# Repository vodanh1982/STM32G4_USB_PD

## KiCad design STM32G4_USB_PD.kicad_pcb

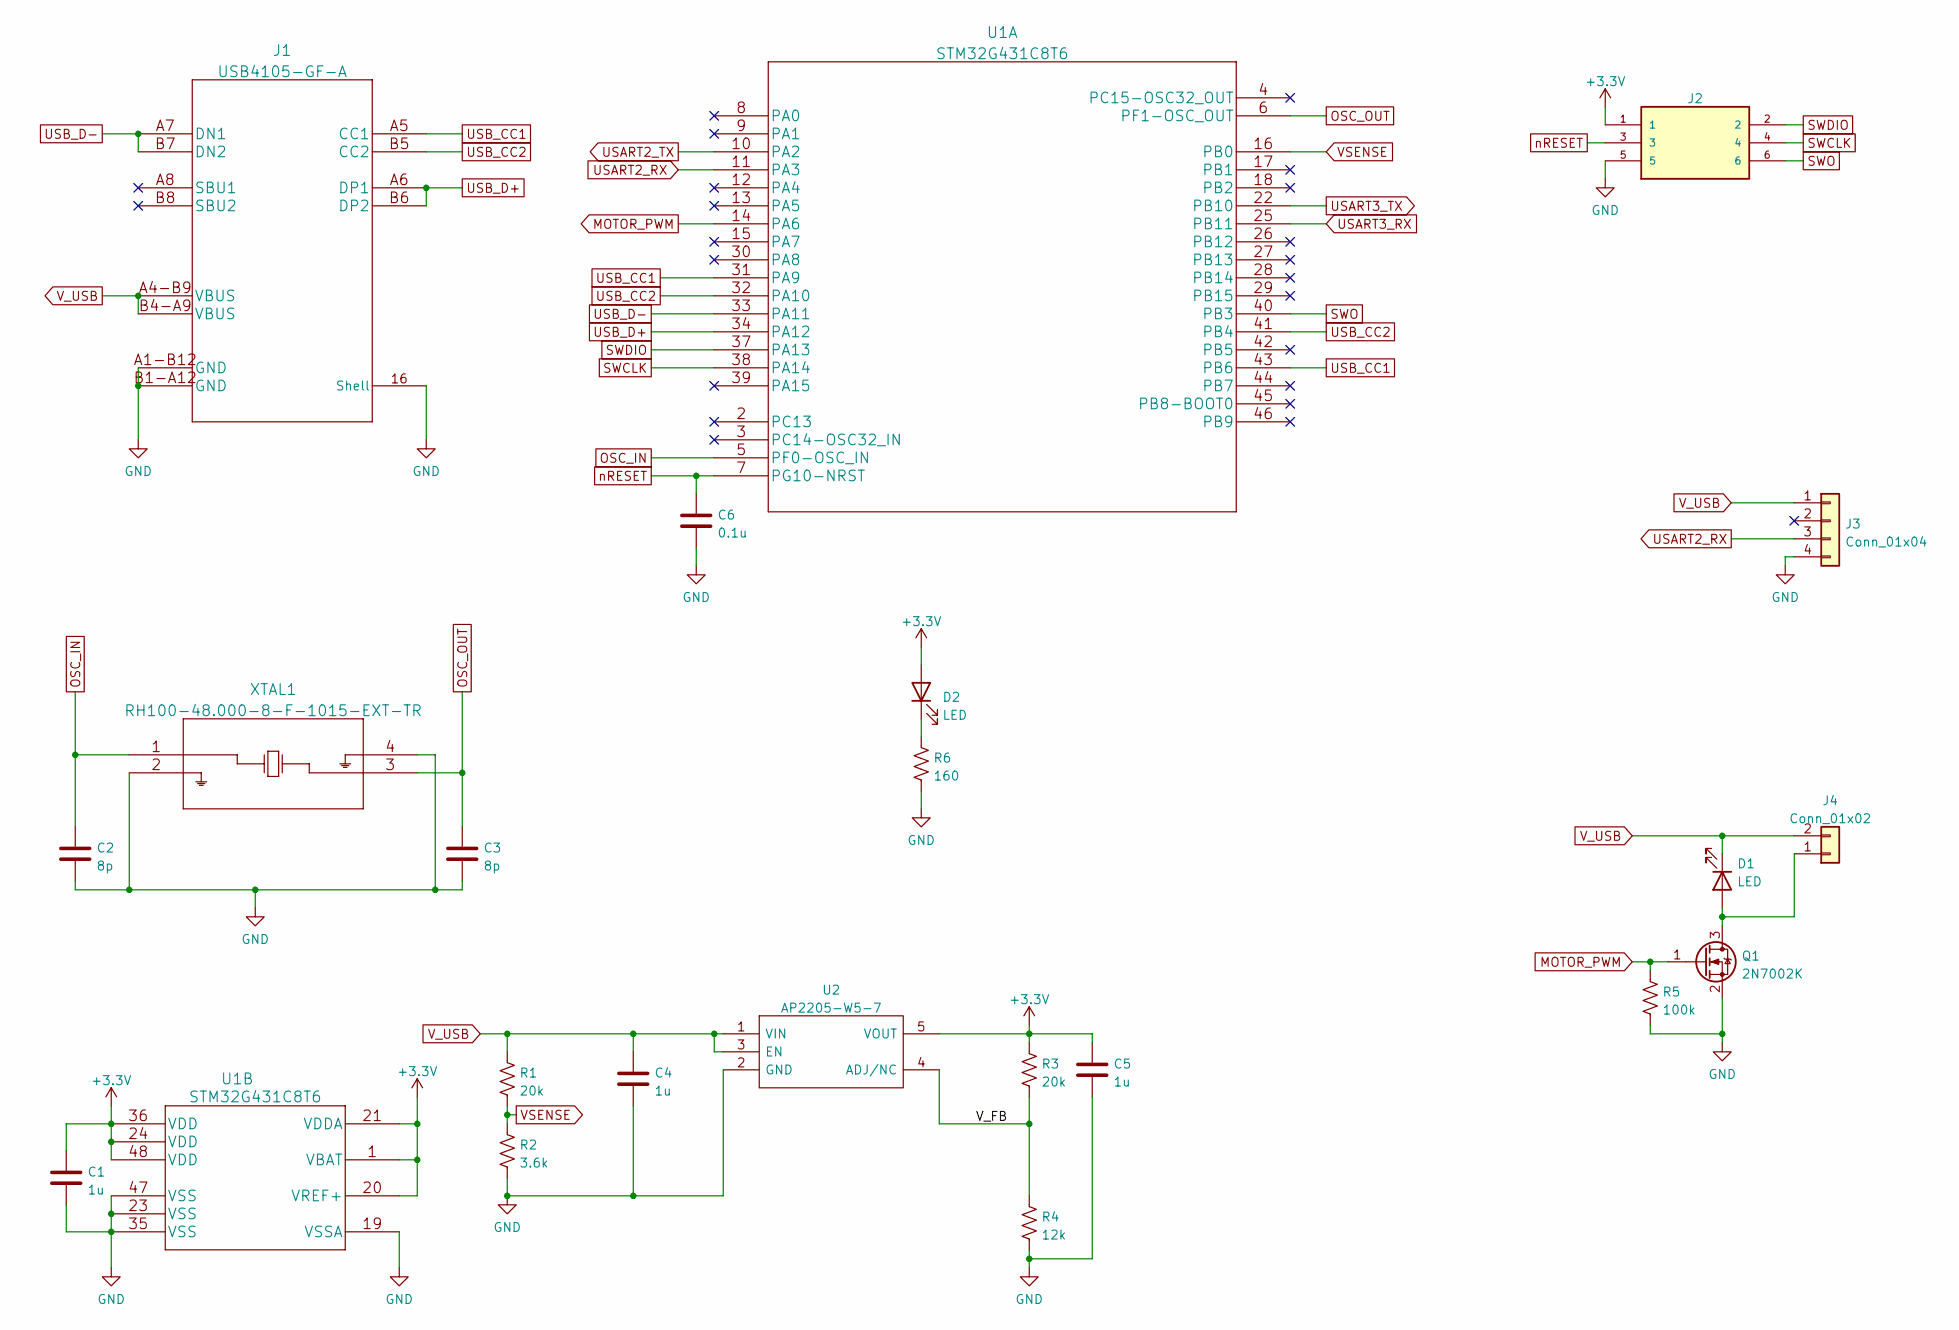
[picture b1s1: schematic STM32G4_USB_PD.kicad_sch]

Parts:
C1, C4, C5: 1u; C_0603_1608Metric_Pad1.08x0.95mm_HandSolder
C2, C3: 8p; C_0201_0603Metric_Pad0.64x0.40mm_HandSolder
C6: 0.1u; C_0201_0603Metric_Pad0.64x0.40mm_HandSolder
D1, D2: LED; LED_0603_1608Metric_Pad1.05x0.95mm_HandSolder
J1: USB4105-GF-A
J2: 8.06.16_J-LINK_6-PIN_NEEDLE_ADAPTER; J-LINK_6-PIN_NEEDLE_ADAPTER; PARTREV A
J3: Conn_01x04; JST_PH_2mm_4
J4: Conn_01x02; JST_PH_2mm_2
Q1: 2N7002K; SOT-23
R1, R3: 20k; R_0603_1608Metric_Pad0.98x0.95mm_HandSolder
R2: 3.6k; R_0603_1608Metric_Pad0.98x0.95mm_HandSolder
R4: 12k; R_0603_1608Metric_Pad0.98x0.95mm_HandSolder
R5: 100k; R_0603_1608Metric_Pad0.98x0.95mm_HandSolder
R6: 160; R_0603_1608Metric_Pad0.98x0.95mm_HandSolder
U1: STM32G431C8T6
U2: AP2205-W5-7; SOT95P282X145-5N; Manufacturer_Part_Number AP2205-W5-7; Mouser Part Number 621-AP2205-W5-7
XTAL1: RH100-48.000-8-F-1015-EXT-TR

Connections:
+3.3V: C1.1, C5.1, D2.2 (A), J2.1, R3.1, U1.1 (VBAT), U1.20 (VREF+), U1.21 (VDDA), U1.24 (VDD), U1.36 (VDD), U1.48 (VDD), U2.5 (VOUT)
/V_FB: R3.2, R4.1, U2.4 (ADJ/NC)
MOTOR_PWM: Q1.1 (G), R5.1, U1.14 (PA6)
unnamed: D1.2 (A), J4.1, Q1.3 (D)
unnamed: D2.1 (K), R6.1
OSC_IN: C2.1, U1.5 (PF0-OSC_IN), XTAL1.1
OSC_OUT: C3.1, U1.6 (PF1-OSC_OUT), XTAL1.3
SWCLK: J2.4, U1.38 (PA14)
SWDIO: J2.2, U1.37 (PA13)
SWO: J2.6, U1.40 (PB3)
USART2_RX: J3.3, U1.11 (PA3)
USART2_TX: U1.10 (PA2)
USART3_RX: U1.25 (PB11)
USART3_TX: U1.22 (PB10)
USB_CC1: J1.A5 (CC1), U1.31 (PA9), U1.43 (PB6)
USB_CC2: J1.B5 (CC2), U1.32 (PA10), U1.41 (PB4)
USB_D+: J1.A6 (DP1), J1.B6 (DP2), U1.34 (PA12)
USB_D-: J1.A7 (DN1), J1.B7 (DN2), U1.33 (PA11)
VSENSE: R1.2, R2.1, U1.16 (PB0)
V_USB: C4.1, D1.1 (K), J1.A4-B9 (VBUS), J1.B4-A9 (VBUS), J3.1, J4.2, R1.1, U2.1 (VIN), U2.3 (EN)
nRESET: C6.1, J2.3, U1.7 (PG10-NRST)

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
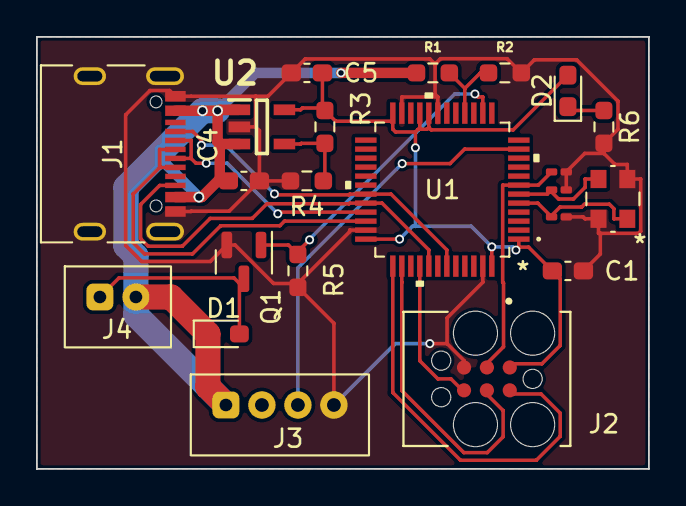
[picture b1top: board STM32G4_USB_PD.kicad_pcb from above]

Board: 2 copper layers, 34.0 x 24.0 mm, 22 parts (0 on the bottom side), 19 nets.

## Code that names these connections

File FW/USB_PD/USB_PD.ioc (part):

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Mcu.Name=STM32G431C(6-8-B)Tx
Mcu.Package=LQFP48
Mcu.UserName=STM32G431C8Tx
PA10.Mode=EnableDeadBattery
PA10.Signal=UCPD1_DBCC2
PA11.Mode=Device
PA11.Signal=USB_DM
PA12.Mode=Device
PA12.Signal=USB_DP
PA2.Mode=Asynchronous
PA2.Signal=USART2_TX
PA3.Mode=Asynchronous
PA3.Signal=USART2_RX
PA6.Signal=S_TIM16_CH1
PA9.Mode=EnableDeadBattery
PA9.Signal=UCPD1_DBCC1
PB0.GPIOParameters=GPIO_Label
PB0.GPIO_Label=VSENSE
PB0.Mode=IN15-Single-Ended
PB0.Signal=ADC1_IN15
PB4.Mode=Sink_AllSignals
PB4.Signal=UCPD1_CC2
PB6.Mode=Sink_AllSignals
PB6.Signal=UCPD1_CC1
RCC.HSE_VALUE=8000000
RCC.SYSCLKFreq_VALUE=16000000
board=custom

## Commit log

2022-09-27 init
2022-09-27 move gerbers files
2022-09-27 add gerbers
2022-10-06 Thicker Trace for VBUS
2022-10-07 improve VBUS trace width
2022-10-07 set GND clearance to 0.2mm
2022-10-21 add usb-C, USB Device and PWM firmware

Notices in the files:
parts and their libraries:
Copyright 2021 Accelerated Designs. All rights reserved.
